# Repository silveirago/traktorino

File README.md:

# Traktorino

Welcome to the Traktorino project! The Traktorino is a low-cost, DIY MIDI controller for DJs. It can control any software that accepts MIDI, such as Traktor, Serato, or Ableton Live. This project is open-source, so you can download all the files for the schematics, enclosure, and code to build one yourself.

## Table of Contents
- [Introduction](#introduction)
- [Parts List](#parts-list)
- [Assembly Instructions](#assembly-instructions)
- [Programming the Arduino](#programming-the-arduino)
- [Setting Up MIDI](#setting-up-midi)
- [Enclosure Assembly](#enclosure-assembly)
- [Troubleshooting](#troubleshooting)
- [Support and Contributions](#support-and-contributions)

## Introduction
Watch the video series on how to build your Traktorino:
1. [Video 1: Introduction and Assembly](https://youtu.be/pawsvbFrXVM)
2. [Video 2: Programming the Arduino](https://youtu.be/B8oFYNJLdgw)
3. [Video 3: Setting Up MIDI](https://youtu.be/18OKo9sQ_s0)
4. [Video 4: Enclosure Assembly](https://youtu.be/xLqzVqaUnkY)

## Parts List
- 1x Traktorino PCB
- 1x Arduino Uno ATmega16U2
- 11x b10k vertical rotary pots
- 3x b10k slide pots - 45mm - 30mm travel (C3031N-1A2-B10K-GP)
- 1x Rotary Encoder
- 2x cd4067 be multiplexers
- 3x 74hc595 bit shifters
- 13x tactile buttons 6x6x9
- 24x 220ohm resistors 
- 1x 1k resistor
- 11x 3mm blue leds 
- 10x 3mm green leds
- 2x 3mm yellow leds
- 2x 3mm red leds

### Parts suggestion

- **Pot 25mm**
https://lcsc.com/product-detail/Potentiometers-Variable-Resistors_ALPS-Electric-RK09D1130C2P_C361173.html

- **Encoder 25mm**
https://www.mouser.com/ProductDetail/Bourns/PEC12R-4025F-N0024?qs=Zq5ylnUbLm4HSBD7%2FFgU%2FA%3D%3D

- **Encoder 20mm**
https://www.mouser.com/ProductDetail/Bourns/PEC11H-4120F-S0020?qs=7MVldsJ5Uaxh8cksqYCfvg%3D%3D 20mm

- **Slide Pot**
https://www.sparkfun.com/products/11621

## Assembly Instructions
1. **Resistors**: Insert and solder the 220 ohm resistors. Place a 1k resistor in the specified position.
2. **Arduino Pin Headers**: Solder the pin headers to the Arduino and snap it onto the PCB.
3. **Multiplexers and Bit Shifters**: Solder these components onto the PCB.
4. **LEDs**: Ensure correct polarity and solder the LEDs.
5. **Tactile Buttons**: Solder the tactile buttons, ensuring correct orientation.
6. **Potentiometers**: Solder the slide and rotary potentiometers.
7. **Rotary Encoder**: Solder the rotary encoder.

## Programming the Arduino
1. Download and install the [Arduino IDE](https://www.arduino.cc/en/software).
2. Clone the Traktorino GitHub repository: `git clone https://github.com/your-repo/traktorino`.
3. Open the Arduino IDE and load the Traktorino code.
4. Install the required libraries: ShiftPWM, MIDI, Multiplexer4067, Thread, and Encoder.
5. Verify the code and upload it to the Arduino Uno.

## Setting Up MIDI
1. **USB MIDI Compatibility**: Use an Arduino Uno with the ATmega16U2 for true USB MIDI compatibility.
2. **DFU Programmer**: Download and install the DFU programmer.
3. **Upload Firmware**: Use the provided `.hex` file to flash the firmware to the ATmega16U2.
4. **Test MIDI**: Use a DAW or MIDI monitoring software to test the MIDI signals from the Traktorino.

## Enclosure Assembly
1. Assemble the plywood enclosure using the provided PDF files.
2. Install the diffusers, spacers, and screws as specified.
3. Attach the button caps and potentiometer knobs.

## Troubleshooting
- If the Traktorino is not functioning, use a multimeter to check for connectivity issues.
- Verify that all components are correctly soldered and oriented.

## Support and Contributions
- Subscribe to the [YouTube channel](https://www.youtube.com/channel/UCyqCwyBJ98fR-CPoyXUxY5w) for updates and tutorials.
- Purchase a Traktorino kit from our store. (Out of stock)
- Check out the [DIY MIDI Controller Workshop](https://go.musiconerd.com/diy-midi-controller-workshop) for more in-depth learning.

## Code Explanation

### PWM Bit Shifter
The code uses a PWM bit shifter for controlling LEDs:
- `ShiftPWM_latchPin`: Set to pin 8.
- To avoid using the SPI port and change the pin numbers, uncomment `#define SHIFTPWM_NOSPI` and set `ShiftPWM_dataPin` and `ShiftPWM_clockPin`.
- `ShiftPWM_invertOutputs`: Set to `false`. Change to `true` if your LEDs turn on when the pin is low.
- `ShiftPWM_balanceLoad`: Set to `false`. Set to `true` to distribute current peaks.

### Libraries
The following libraries are included:
- **ShiftPWM** for PWM control.
- **MIDI** by Forty Seven Effects for MIDI communication.
- **Multiplexer4067** for handling the CD4067 multiplexer.
- **Thread** and **ThreadController** by Ivan Seidel for managing multiple tasks.
- **Encoder** by Paul Stoffregen for handling rotary encoders.

### Buttons
- `muxNButtons`: Number of digital inputs used in the multiplexer.
- `NButtons`: Number of direct digital inputs used.
- `muxButtonPin` and `buttonPin`: Arrays to store the pins used for buttons.

### Debounce
- `lastDebounceTime` and `debounceDelay`: Used to handle debounce for button presses.

### Potentiometers
- `NPots`: Number of analog inputs used.
- `muxPotPin`: Array to store the pins used for potentiometers.

### Potentiometer Reading
- `TIMEOUT`: Time the potentiometer will be read after exceeding `varThreshold`.
- `varThreshold`: Threshold for potentiometer signal variation.

### Encoder
- `myEnc`: Instance of the `Encoder` library using pins 3 and 2.
- `oldPosition`: Previous position of the encoder.

### MIDI Configuration
- `midiCh`, `note`, and `cc`: MIDI channel, note, and CC configurations.

### LEDs
- Configuration for controlling 24 LEDs with PWM.
- VU meter and button LED pins are defined.

### Multiplexer
- Instances of `Multiplexer4067` for pots and buttons.

### Threads
- `ThreadController` for managing tasks.
- Separate threads for reading potentiometers and buttons.

### Setup and Loop
In `setup()`, the serial communication is initialized, MIDI thru is turned off, multiplexers and LEDs are initialized, and threads are configured.

In `loop()`, the main tasks such as reading MIDI, encoder, and running threads are handled.

### Functions
- `readButtons()`: Reads button states and sends MIDI note messages.
- `readPots()`: Reads potentiometer states and sends MIDI control change messages.
- `readEncoder()`: Reads encoder values and sends MIDI control change messages.
- `handleControlChange()`, `handleNoteOn()`, and `handleNoteOff()`: Handle LED feedback for MIDI control changes and note messages.

## Usage
- Connect your Arduino and load the provided code.
- Ensure all components (buttons, potentiometers, LEDs) are connected to the specified pins.
- Install the required libraries mentioned above.
- Upload the code to your Arduino and start using your Traktorino MIDI controller with your favorite DJ software.

Feel free to modify the code and configurations to fit your specific needs. Happy DJing!

---

**Author**: Gustavo Silveira

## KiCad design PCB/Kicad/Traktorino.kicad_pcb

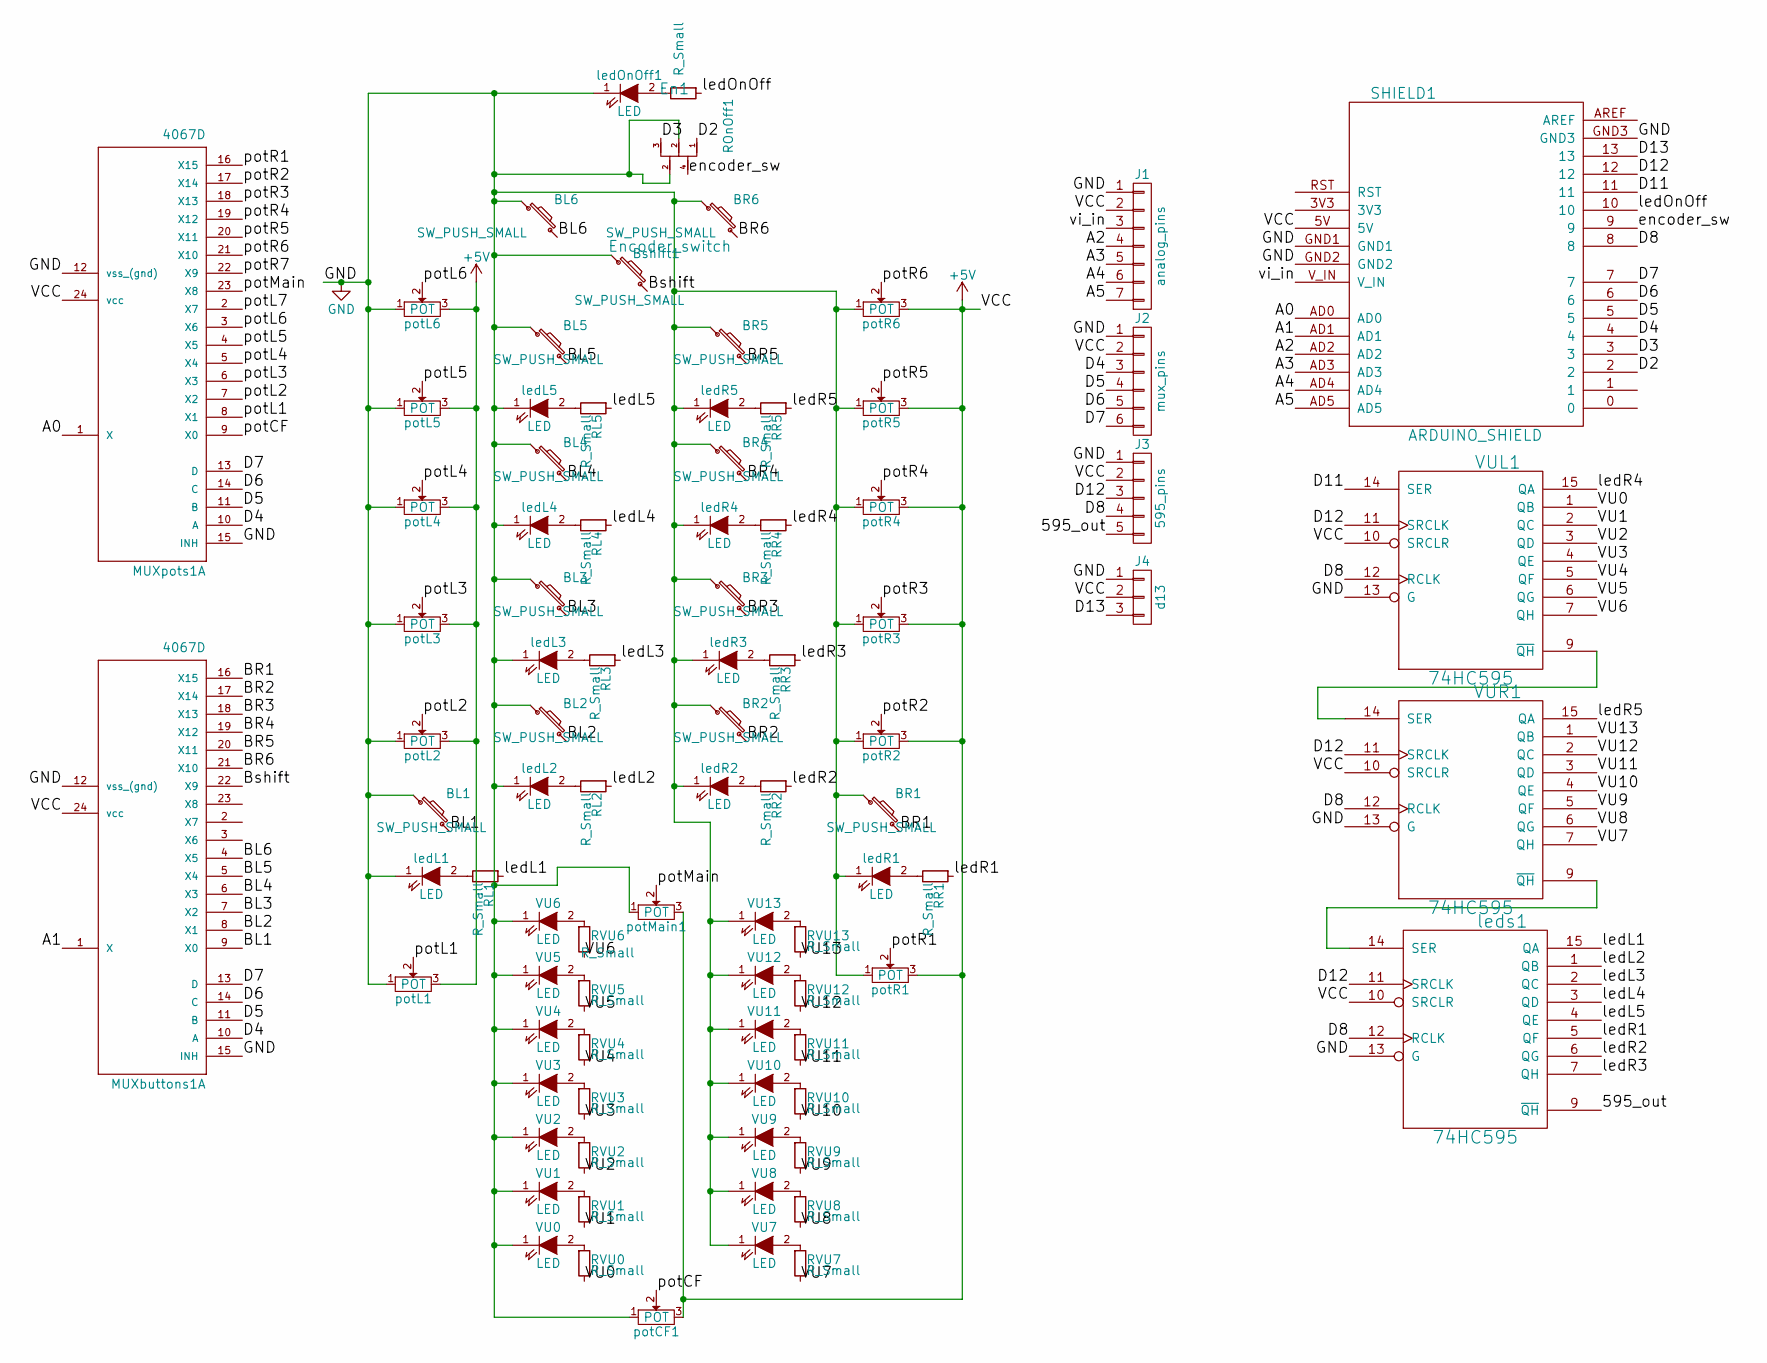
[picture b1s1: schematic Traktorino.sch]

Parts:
BL1, BL2, BL3, BL4, BL5, BL6: SW_PUSH_SMALL; SW_tactile
BR1, BR2, BR3, BR4, BR5, BR6: SW_PUSH_SMALL; SW_tactile
Bshift1: SW_PUSH_SMALL; SW_tactile
En1: Encoder_switch; SF-ROTARY-ENCODER_gus
J1: analog_pins; Pin_Header_Straight_1x07_Pitch2.54mm
J2: mux_pins; Pin_Header_Straight_1x06_Pitch2.54mm
J3: 595_pins; Pin_Header_Straight_1x05_Pitch2.54mm
J4: d13; Pin_Header_Straight_1x03_Pitch2.54mm
MUXbuttons1: 4067D; 40xx-DIL24-6
MUXpots1: 4067D; 40xx-DIL24-6
RL1, RL2, RL3, RL4, RL5: R_Small; Resistor_Horizontal_RM7mm
ROnOff1: R_Small; Resistor_Horizontal_RM7mm
RR1, RR2, RR3, RR4, RR5: R_Small; Resistor_Horizontal_RM7mm
RVU0, RVU1, RVU2, RVU3, RVU4, RVU5, RVU6, RVU7, RVU8, RVU9, RVU10, RVU11, RVU12, RVU13: R_Small; Resistor_Horizontal_RM7mm
SHIELD1: ARDUINO_SHIELD; ARDUINO_SHIELD_2_040pins
VU0, VU1, VU2, VU3, VU4, VU5, VU6, VU7, VU8, VU9, VU10, VU11, VU12, VU13: LED; LED-3MM
VUL1: 74HC595; DIL16
VUR1: 74HC595; DIL16
ledL1, ledL2, ledL3, ledL4, ledL5: LED; LED-3MM
ledOnOff1: LED; LED-3MM
ledR1, ledR2, ledR3, ledR4, ledR5: LED; LED-3MM
leds1: 74HC595; DIL16
potCF1: POT; Slide_Potentiometer
potL1: POT; Slide_Potentiometer
potL2, potL3, potL4, potL5, potL6: POT; Pot_vertical
potMain1: POT; Pot_vertical
potR1: POT; Slide_Potentiometer
potR2, potR3, potR4, potR5, potR6: POT; Pot_vertical

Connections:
+5V: J1.2, J2.2, J3.2, J4.2, MUXbuttons1.24 (vcc), MUXpots1.24 (vcc), SHIELD1.5V, VUL1.10 (SRCLR), VUL1.16 (VCC), VUR1.10 (SRCLR), VUR1.16 (VCC), leds1.10 (SRCLR), leds1.16 (VCC), potCF1.3, potL1.3, potL2.3, potL3.3, potL4.3, potL5.3, potL6.3, potMain1.3, potR1.3, potR2.3, potR3.3, potR4.3, potR5.3, potR6.3
/595_out: J3.5, leds1.9 (~QH)
/A0: MUXpots1.1 (X), SHIELD1.AD0
/A1: MUXbuttons1.1 (X), SHIELD1.AD1
/A2: J1.4, SHIELD1.AD2
/A3: J1.5, SHIELD1.AD3
/A4: J1.6, SHIELD1.AD4
/A5: J1.7, SHIELD1.AD5
/BL1: BL1.2, MUXbuttons1.9 (X0)
/BL2: BL2.2, MUXbuttons1.8 (X1)
/BL3: BL3.2, MUXbuttons1.7 (X2)
/BL4: BL4.2, MUXbuttons1.6 (X3)
/BL5: BL5.2, MUXbuttons1.5 (X4)
/BL6: BL6.2, MUXbuttons1.4 (X5)
/BR1: BR1.2, MUXbuttons1.16 (X15)
/BR2: BR2.2, MUXbuttons1.17 (X14)
/BR3: BR3.2, MUXbuttons1.18 (X13)
/BR4: BR4.2, MUXbuttons1.19 (X12)
/BR5: BR5.2, MUXbuttons1.20 (X11)
/BR6: BR6.2, MUXbuttons1.21 (X10)
/Bshift: Bshift1.2, MUXbuttons1.22 (X9)
/D2: En1.1, SHIELD1.2
/D3: En1.3, SHIELD1.3
/D4: J2.3, MUXbuttons1.10 (A), MUXpots1.10 (A), SHIELD1.4
/D5: J2.4, MUXbuttons1.11 (B), MUXpots1.11 (B), SHIELD1.5
/D6: J2.5, MUXbuttons1.14 (C), MUXpots1.14 (C), SHIELD1.6
/D7: J2.6, MUXbuttons1.13 (D), MUXpots1.13 (D), SHIELD1.7
/D8: J3.4, SHIELD1.8, VUL1.12 (RCLK), VUR1.12 (RCLK), leds1.12 (RCLK)
/D11: SHIELD1.11, VUL1.14 (SER)
/D12: J3.3, SHIELD1.12, VUL1.11 (SRCLK), VUR1.11 (SRCLK), leds1.11 (SRCLK)
/D13: J4.3, SHIELD1.13
/VU0: RVU0.2, VUL1.1 (QB)
/VU1: RVU1.2, VUL1.2 (QC)
/VU2: RVU2.2, VUL1.3 (QD)
/VU3: RVU3.2, VUL1.4 (QE)
/VU4: RVU4.2, VUL1.5 (QF)
/VU5: RVU5.2, VUL1.6 (QG)
/VU6: RVU6.2, VUL1.7 (QH)
/VU7: RVU7.2, VUR1.7 (QH)
/VU8: RVU8.2, VUR1.6 (QG)
/VU9: RVU9.2, VUR1.5 (QF)
/VU10: RVU10.2, VUR1.4 (QE)
/VU11: RVU11.2, VUR1.3 (QD)
/VU12: RVU12.2, VUR1.2 (QC)
/VU13: RVU13.2, VUR1.1 (QB)
/encoder_sw: En1.4, SHIELD1.9
/ledL1: RL1.1, leds1.15 (QA)
/ledL2: RL2.1, leds1.1 (QB)
/ledL3: RL3.1, leds1.2 (QC)
/ledL4: RL4.1, leds1.3 (QD)
/ledL5: RL5.1, leds1.4 (QE)
/ledOnOff: ROnOff1.1, SHIELD1.10
/ledR1: RR1.1, leds1.5 (QF)
/ledR2: RR2.1, leds1.6 (QG)
/ledR3: RR3.1, leds1.7 (QH)
/ledR4: RR4.1, VUL1.15 (QA)
/ledR5: RR5.1, VUR1.15 (QA)
/potCF: MUXpots1.9 (X0), potCF1.2
/potL1: MUXpots1.8 (X1), potL1.2
/potL2: MUXpots1.7 (X2), potL2.2
/potL3: MUXpots1.6 (X3), potL3.2
/potL4: MUXpots1.5 (X4), potL4.2
/potL5: MUXpots1.4 (X5), potL5.2
/potL6: MUXpots1.3 (X6), potL6.2
/potL7: MUXpots1.2 (X7)
/potMain: MUXpots1.23 (X8), potMain1.2
/potR1: MUXpots1.16 (X15), potR1.2
/potR2: MUXpots1.17 (X14), potR2.2
/potR3: MUXpots1.18 (X13), potR3.2
/potR4: MUXpots1.19 (X12), potR4.2
/potR5: MUXpots1.20 (X11), potR5.2
/potR6: MUXpots1.21 (X10), potR6.2
/potR7: MUXpots1.22 (X9)
/vi_in: J1.3, SHIELD1.V_IN
GND: BL1.1, BL2.1, BL3.1, BL4.1, BL5.1, BL6.1, BR1.1, BR2.1, BR3.1, BR4.1, BR5.1, BR6.1, Bshift1.1, En1.2, J1.1, J2.1, J3.1, J4.1, MUXbuttons1.12 (vss_(gnd)), MUXbuttons1.15 (INH), MUXpots1.12 (vss_(gnd)), MUXpots1.15 (INH), SHIELD1.GND1, SHIELD1.GND2, SHIELD1.GND3, VU0.1 (K), VU1.1 (K), VU2.1 (K), VU3.1 (K), VU4.1 (K), VU5.1 (K), VU6.1 (K), VU7.1 (K), VU8.1 (K), VU9.1 (K), VU10.1 (K), VU11.1 (K), VU12.1 (K), VU13.1 (K), VUL1.8 (GND), VUL1.13 (G), VUR1.8 (GND), VUR1.13 (G), ledL1.1 (K), ledL2.1 (K), ledL3.1 (K), ledL4.1 (K), ledL5.1 (K), ledOnOff1.1 (K), ledR1.1 (K), ledR2.1 (K), ledR3.1 (K), ledR4.1 (K), ledR5.1 (K), leds1.8 (GND), leds1.13 (G), potCF1.1, potL1.1, potL2.1, potL3.1, potL4.1, potL5.1, potL6.1, potMain1.1, potR1.1, potR2.1, potR3.1, potR4.1, potR5.1, potR6.1
unnamed: RL1.2, ledL1.2 (A)
unnamed: RL2.2, ledL2.2 (A)
unnamed: RL3.2, ledL3.2 (A)
unnamed: RL4.2, ledL4.2 (A)
unnamed: RL5.2, ledL5.2 (A)
unnamed: ROnOff1.2, ledOnOff1.2 (A)
unnamed: RR1.2, ledR1.2 (A)
unnamed: RR2.2, ledR2.2 (A)
unnamed: RR3.2, ledR3.2 (A)
unnamed: RR4.2, ledR4.2 (A)
unnamed: RR5.2, ledR5.2 (A)
unnamed: RVU0.1, VU0.2 (A)
unnamed: RVU1.1, VU1.2 (A)
unnamed: RVU2.1, VU2.2 (A)
unnamed: RVU3.1, VU3.2 (A)
unnamed: RVU4.1, VU4.2 (A)
unnamed: RVU5.1, VU5.2 (A)
unnamed: RVU6.1, VU6.2 (A)
unnamed: RVU7.1, VU7.2 (A)
unnamed: RVU8.1, VU8.2 (A)
unnamed: RVU9.1, VU9.2 (A)
unnamed: RVU10.1, VU10.2 (A)
unnamed: RVU11.1, VU11.2 (A)
unnamed: RVU12.1, VU12.2 (A)
unnamed: RVU13.1, VU13.2 (A)
unnamed: VUL1.9 (~QH), VUR1.14 (SER)
unnamed: VUR1.9 (~QH), leds1.14 (SER)

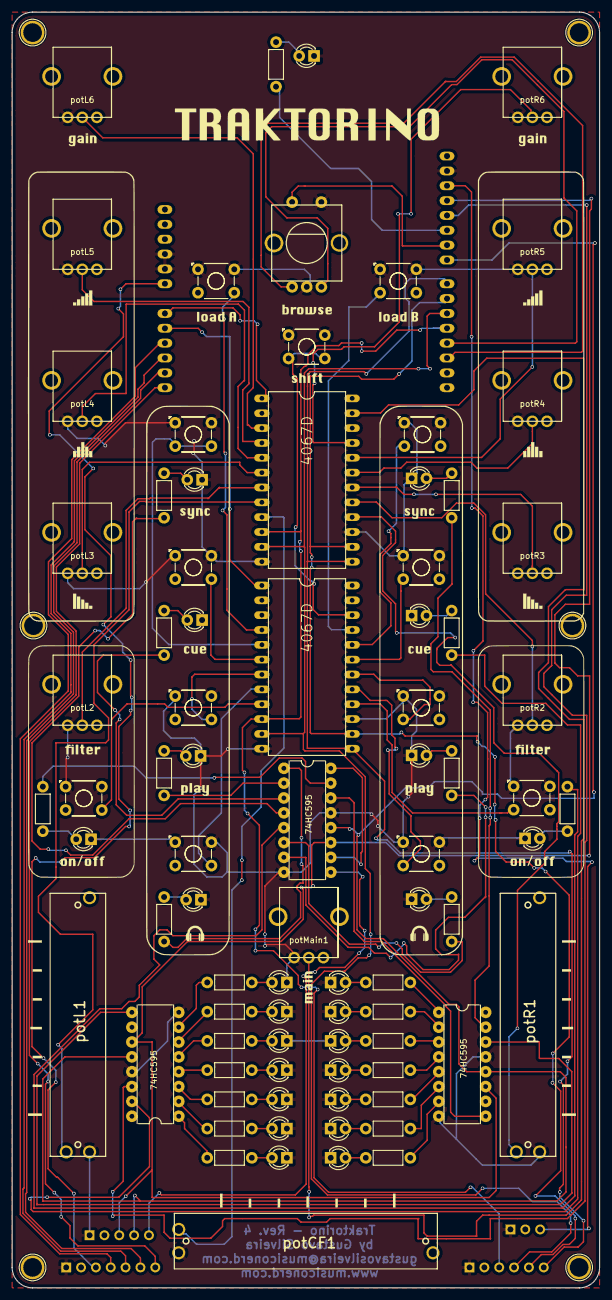
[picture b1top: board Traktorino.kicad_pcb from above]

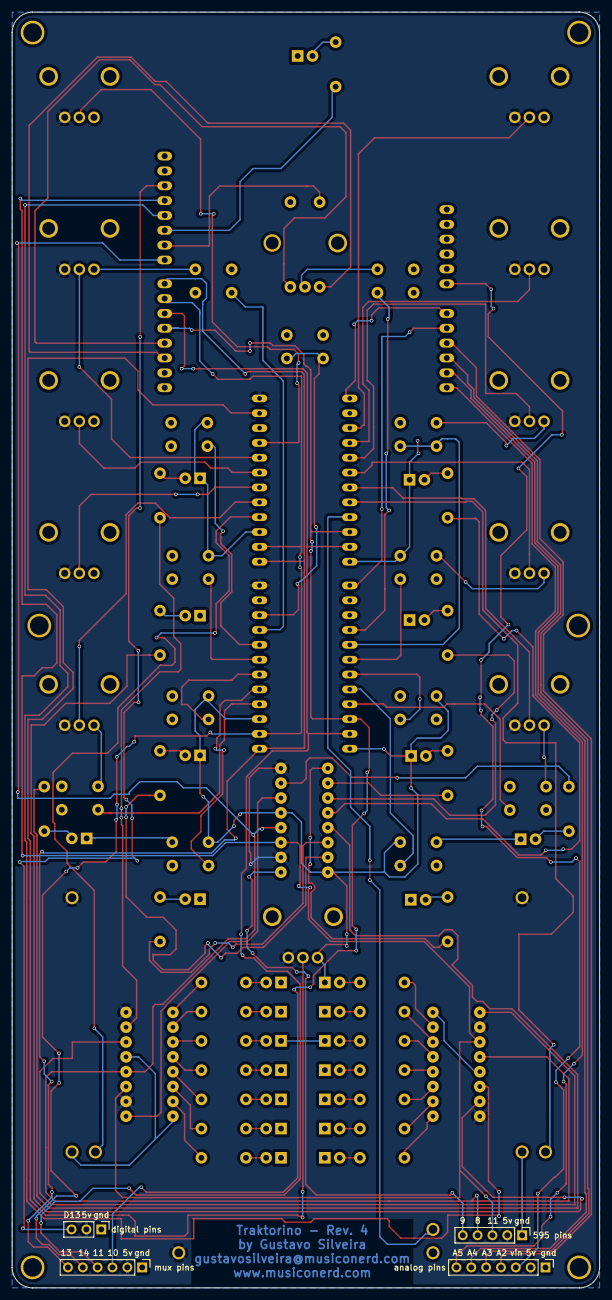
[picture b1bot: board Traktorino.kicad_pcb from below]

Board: 2 copper layers, 100.5 x 218.2 mm, 88 parts (4 on the bottom side), 100 nets.

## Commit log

2018-03-14 Traktorino files added
2018-03-14 Gerber files
2018-04-27 gerber updated
2018-05-07 enclosure
2018-06-15 Encoder fixed
2018-06-15 Encoder fixed
    And other bugs fixed
2018-06-16 Enclosure update
2018-06-23 Code updated
2018-06-24 Conde updated
    Added some links
2018-06-27 traktor mapping added
2018-07-02 PCB update
    Bigger solder masks for components. Some components had their legs spaced so they have a better fit.
    Free pins of the Arduino exposed.
2018-07-02 Gerber files updated
2018-07-02 PCB updated
    Names added to the exposed pins.
2018-07-02 pcb updated
2018-07-06 Pdcb and enclosure update
    PCB rev. 4! Arduino and mux pins exposed.
    Enclosure's thongue was shortened so it doesn't collide with the chroma caps faders.
2018-07-07 Enclosure update
    Put a missing "on/off".
    Adjusted the 12x24 sheet.
2018-07-09 Acrylic enclosure layout added
2020-03-24 fixes button reads from digital pins; enables browse encoder click
    added pinMode(..., INPUT_PULLUP) on buttons attached to digital pins in setup()
    added a button on pin 9 to enable browse encoder click detection
2020-03-24 turn off soft MIDI Thru
    turn off soft MIDI Thru, prevents some DJ software from creating an infinite send/receive loop
2020-03-24 Enable button reads on all free digital pins
    Enables buttons on free digital pins, including:
    - pin 9 for encoder click
    - pin 16 on front headers
    - pins A2, A3, A4, and A5 on front headers
2020-03-24 Enables buttons on free digital pins
    Enables buttons on free digital pins, including:
    pin 9 for encoder click
    pin 16 on front headers
    pins A2, A3, A4, and A5 on front headers
2020-04-13 Encoder click button added
2020-04-13 Encoder click added
2020-06-08 switch to StaticThreadController
    switch to StaticThreadController (from ThreadController) for speed gains
2020-06-09 add placeholder code for pots on analog pins
    add placeholder code for pots on analog pins
2020-06-10 adds suport for buttons and potentiometers on an add-on 4067 multiplexer
    adds suport for buttons and potentiometers on an add-on 4067 multiplexer
2020-06-10 Create notes.txt
    added notes.txt, brief details on how to add an add-on 4067 mux
2020-06-10 remove unusde lines of code
    remove unusde lines of code
2020-06-10 code cleanup
    code cleanup
2020-06-10 consolidate midi channel usage
    consolidate midi channel usage
2020-06-10 switch to Multiplexer4067Fast library
    switch to Multiplexer4067Fast library
2020-06-10 put add-on mux code behind an #include / #define
    put add-on mux code behind an #include / #define
2020-06-10 limit number of mux readings to 1
    limit number of mux readings to 1
2020-06-10 put additional buttons and pots behind an #include / #define
    put additional buttons and pots behind an #include / #define
2020-06-10 add hex file for arduino mega
    add hex file for arduino mega
2020-06-10 add rasprague to comments
    add rasprague to comments
2020-06-11 fix #define typo
    fix #define typo
2020-12-11 Kicad files added
2024-06-11 wiki added
2024-10-03 added 3mm info on the enclosure
2024-10-04 parts updated
